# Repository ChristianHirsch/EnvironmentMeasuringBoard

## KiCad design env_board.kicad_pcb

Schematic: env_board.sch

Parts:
C1: 1u; C_0603_1608Metric
C6, C9: 0.1u; C_0603_1608Metric
C7: 4.7u; C_0603_1608Metric
C8: 200n; C_0603_1608Metric
J1: CONN_01X07; PinHeader_1x07_P2.54mm_Vertical
R1, R3, R4: 10k; R_0603_1608Metric
R6, R9, R10: 100k; R_0603_1608Metric
U1: RFD77101; RFDigital_RFD77101
U2: ENS210; AMS_QFN-4-1EP_2x2mm_P0.95mm_EP0.7x1.6mm
U3: CCS811; AMS_LGA-10-1EP_2.7x4mm_P0.6mm
U6: BMP280; Bosch_LGA-8_2x2.5mm_P0.65mm_ClockwisePinNumbering
U7: SST26VF016B; SOIC-8_3.9x4.9mm_P1.27mm

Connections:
/BATT_V: U1.24; also elsewhere on the board
/BATT_V_EN: U1.11; also elsewhere on the board
/CCS_WAKE: U1.27, U3.7
/FLASH_CS: R10.2, U1.31, U7.1
/FLASH_SCK: U1.32, U7.6
/FLASH_SI: U1.21, U7.5
/FLASH_SO: U1.22, U7.2
/GPIO0: J1.6, U1.25
/GPIO1: J1.7, U1.23
/SCL: R3.2, U1.28, U2.2, U3.10, U6.4
/SDA: R1.2, U1.26, U2.3, U3.9, U6.3
/SWDCLK: J1.5, U1.9
/SWDIO/RESET: J1.4, U1.8
GND: C1.2, C6.2, C7.2, C8.2, C9.2, J1.1, U1.1, U1.2, U1.4, U1.6, U1.19, U1.30, U1.42, U1.43, U1.44, U1.45, U2.4, U2.5, U3.11, U6.1, U6.7, U7.4; also elsewhere on the board
unnamed: R4.2, U3.2
unnamed: R6.2, U7.7
unnamed: R9.2, U7.3
unnamed: U3.4, U3.5
VBUS: J1.3; also elsewhere on the board
VDD: C1.1, C6.1, C7.1, C8.1, C9.1, R1.1, R3.1, R4.1, R6.1, R9.1, R10.1, U1.7, U2.1, U3.1, U3.6, U6.2, U6.5, U6.6, U6.8, U7.8; also elsewhere on the board

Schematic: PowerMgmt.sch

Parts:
C2, C3: 4.7u; C_0603_1608Metric
C4, C5: 1u; C_0603_1608Metric
D1, D2: BAT20J; D_SOD-323
J2: BATT_CONN; JST_PH_S2B-PH-K_1x02_P2.00mm_Horizontal
P1: USB_OTG; USB_Micro-B_Molex_47346-0001
Q1: NX7002AKVL; SOT-23
Q2, Q3: DMP3099L-13; SOT-23
R2: 3.3k; R_0603_1608Metric
R5, R8: 10k; R_0603_1608Metric
R7: 8.2k; R_0603_1608Metric
U4: TLV74130; SOT-23-5
U5: MCP73811T-420I-OT; SOT-23-5

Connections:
+BATT: C3.1, J2.1, Q2.3, Q3.2, R5.1, U5.3 (VBAT)
/BATT_V: R2.2, R7.1; also elsewhere on the board
/BATT_V_EN: Q1.1; also elsewhere on the board
GND: C2.2, C3.2, C4.2, C5.2, J2.2, P1.5, Q1.2, R7.2, R8.2, U4.2 (GND), U5.2 (VSS); also elsewhere on the board
unnamed: C2.1, D1.2, P1.1, U5.1 (CEN), U5.4 (VDD), U5.5 (PROG)
unnamed: C4.1, D2.1, Q2.2, U4.1 (VIN), U4.3 (EN)
unnamed: Q1.3, Q3.1, R5.2
unnamed: Q3.3, R2.1
VBUS: D1.1, D2.2, Q2.1, R8.1; also elsewhere on the board
VDD: C5.1, U4.5 (VOUT); also elsewhere on the board

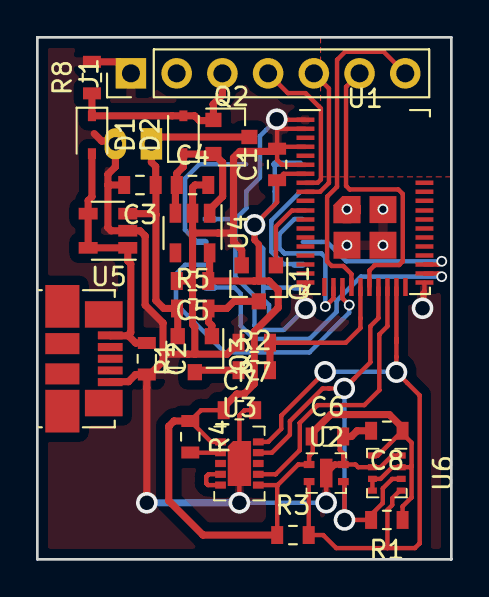
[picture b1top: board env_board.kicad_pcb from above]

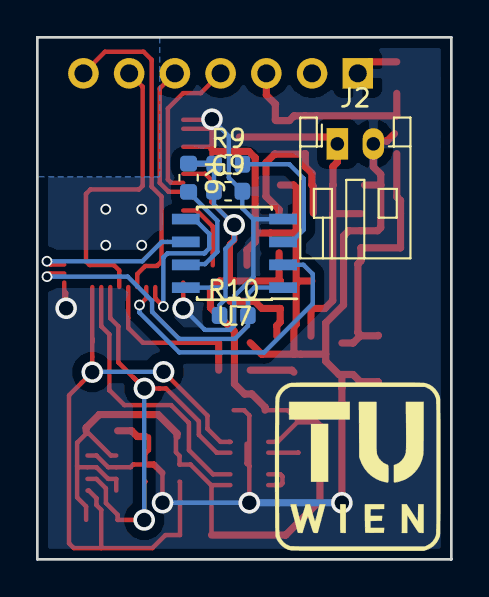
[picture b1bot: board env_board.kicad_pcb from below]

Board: 2 copper layers, 23.0 x 29.0 mm, 34 parts (6 on the bottom side), 25 nets.

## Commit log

2017-11-07 update schematics
2017-11-07 update pcb
2017-11-07 add cache lib
2017-11-07 update board, schematics, add bmp280
2018-01-31 changes to use nRF52840 instead of simblee
2018-03-12 update sensor and add housing for sensor
2018-04-09 update sensor/housings
2018-05-15 update housing for new sensor
2018-07-31 rc2.0
2018-07-31 add flash memory
2018-07-31 update gitignore
2018-11-15 update project
